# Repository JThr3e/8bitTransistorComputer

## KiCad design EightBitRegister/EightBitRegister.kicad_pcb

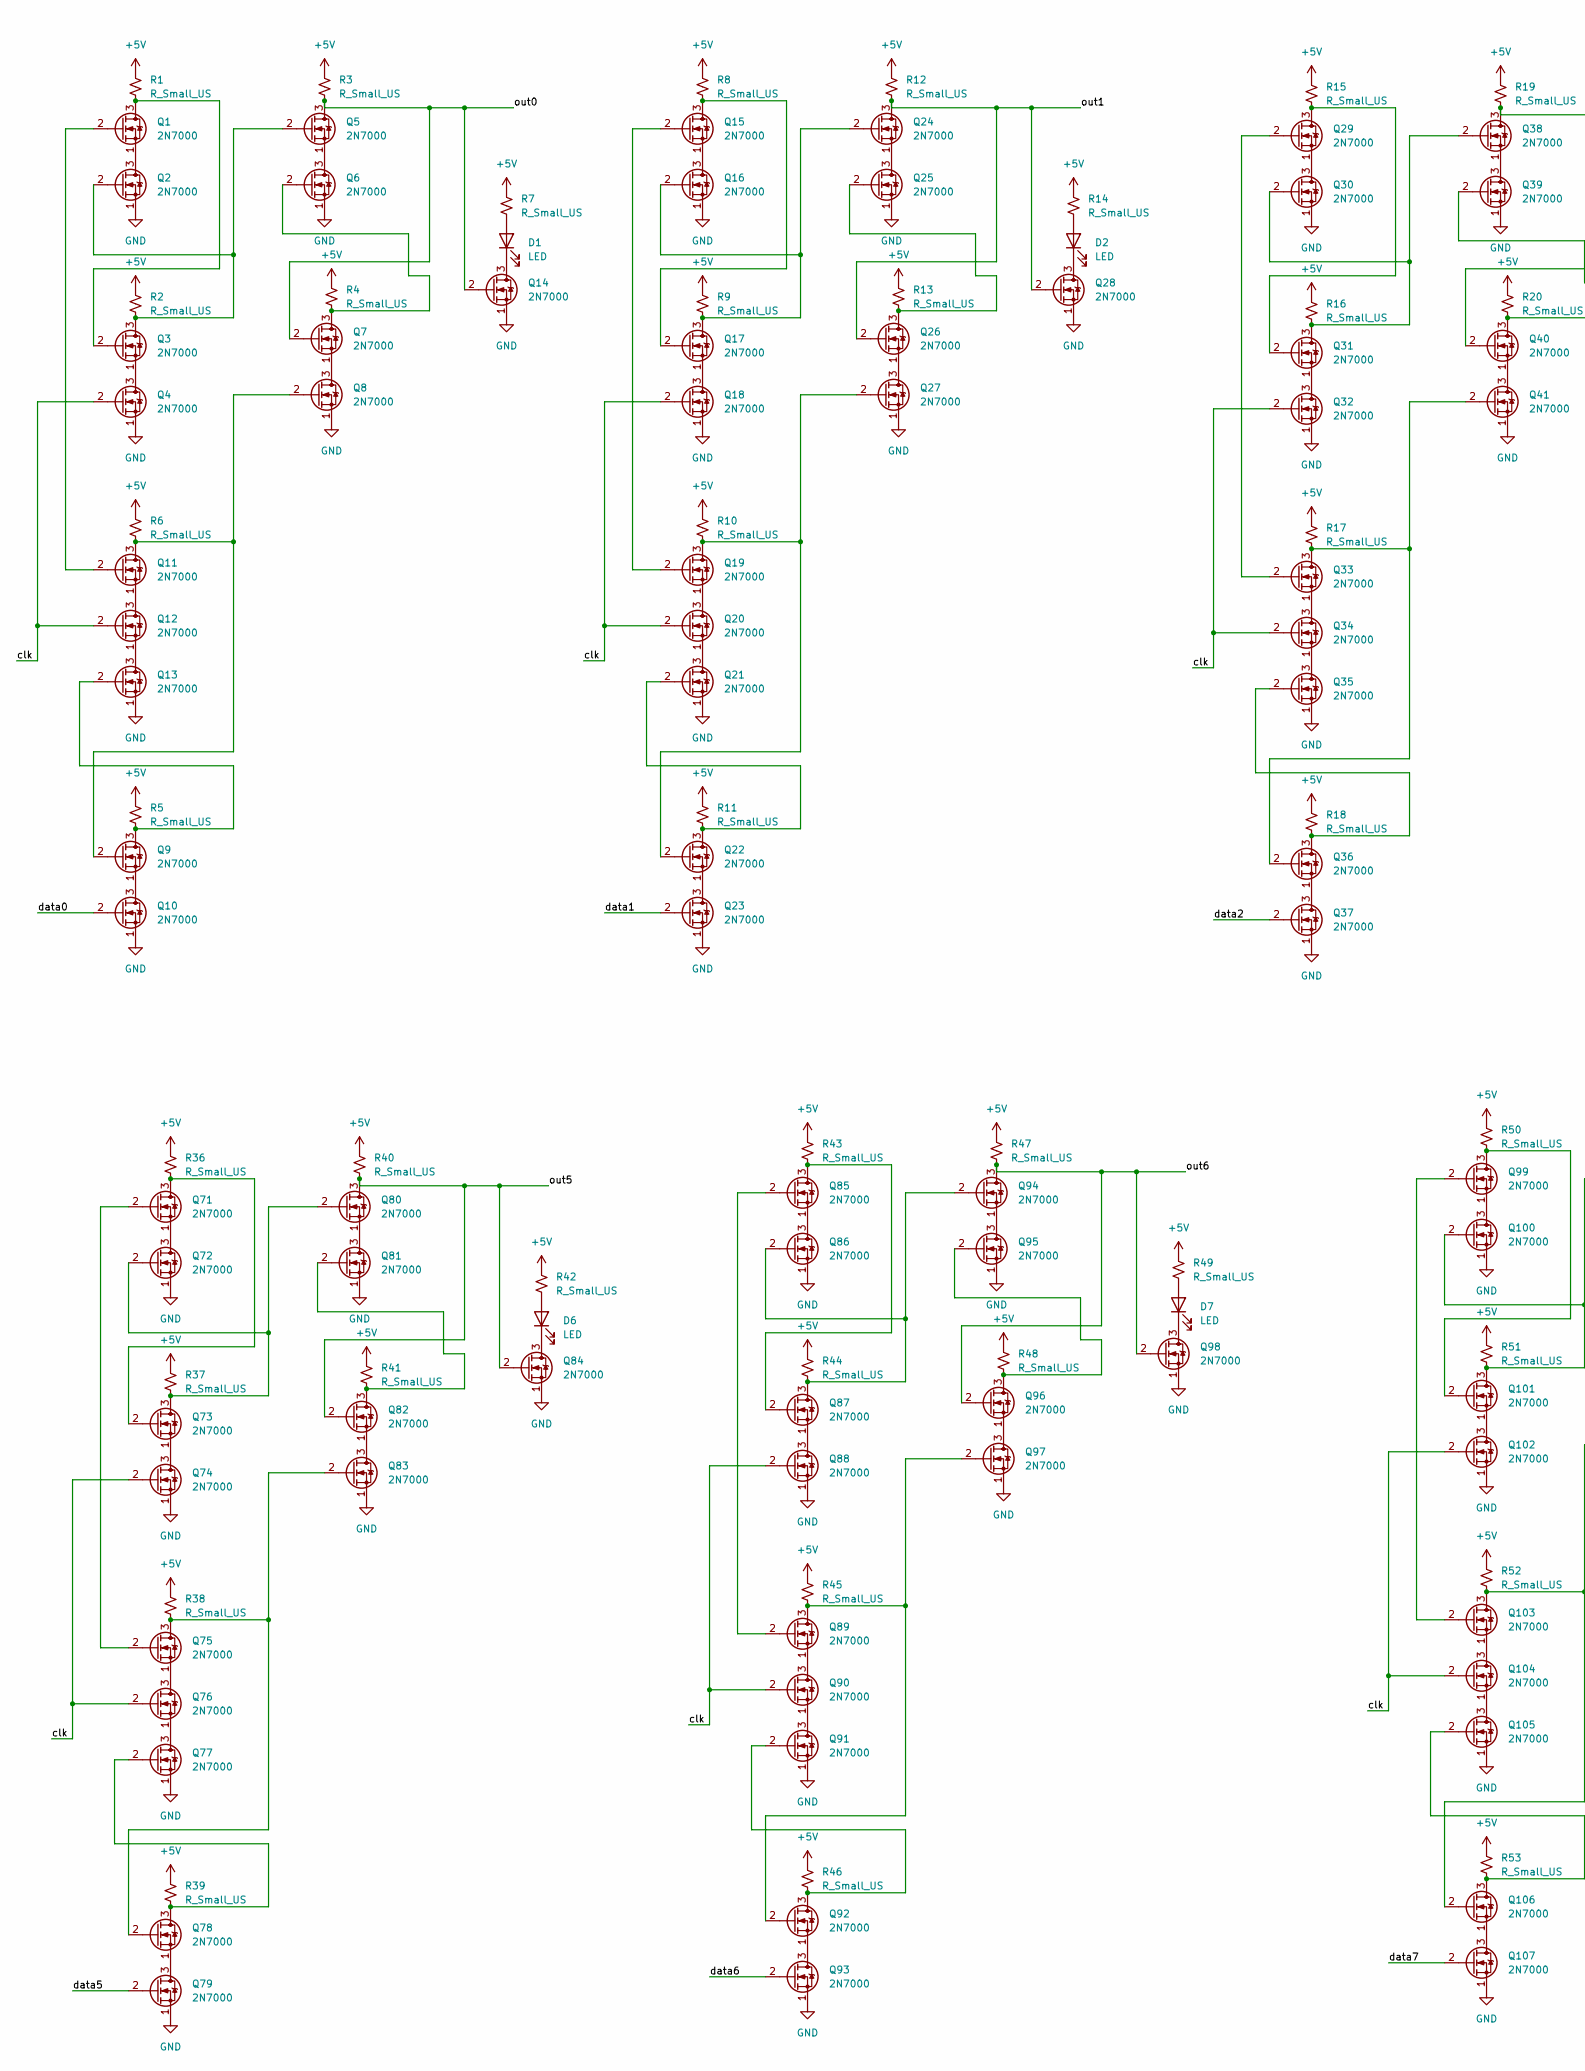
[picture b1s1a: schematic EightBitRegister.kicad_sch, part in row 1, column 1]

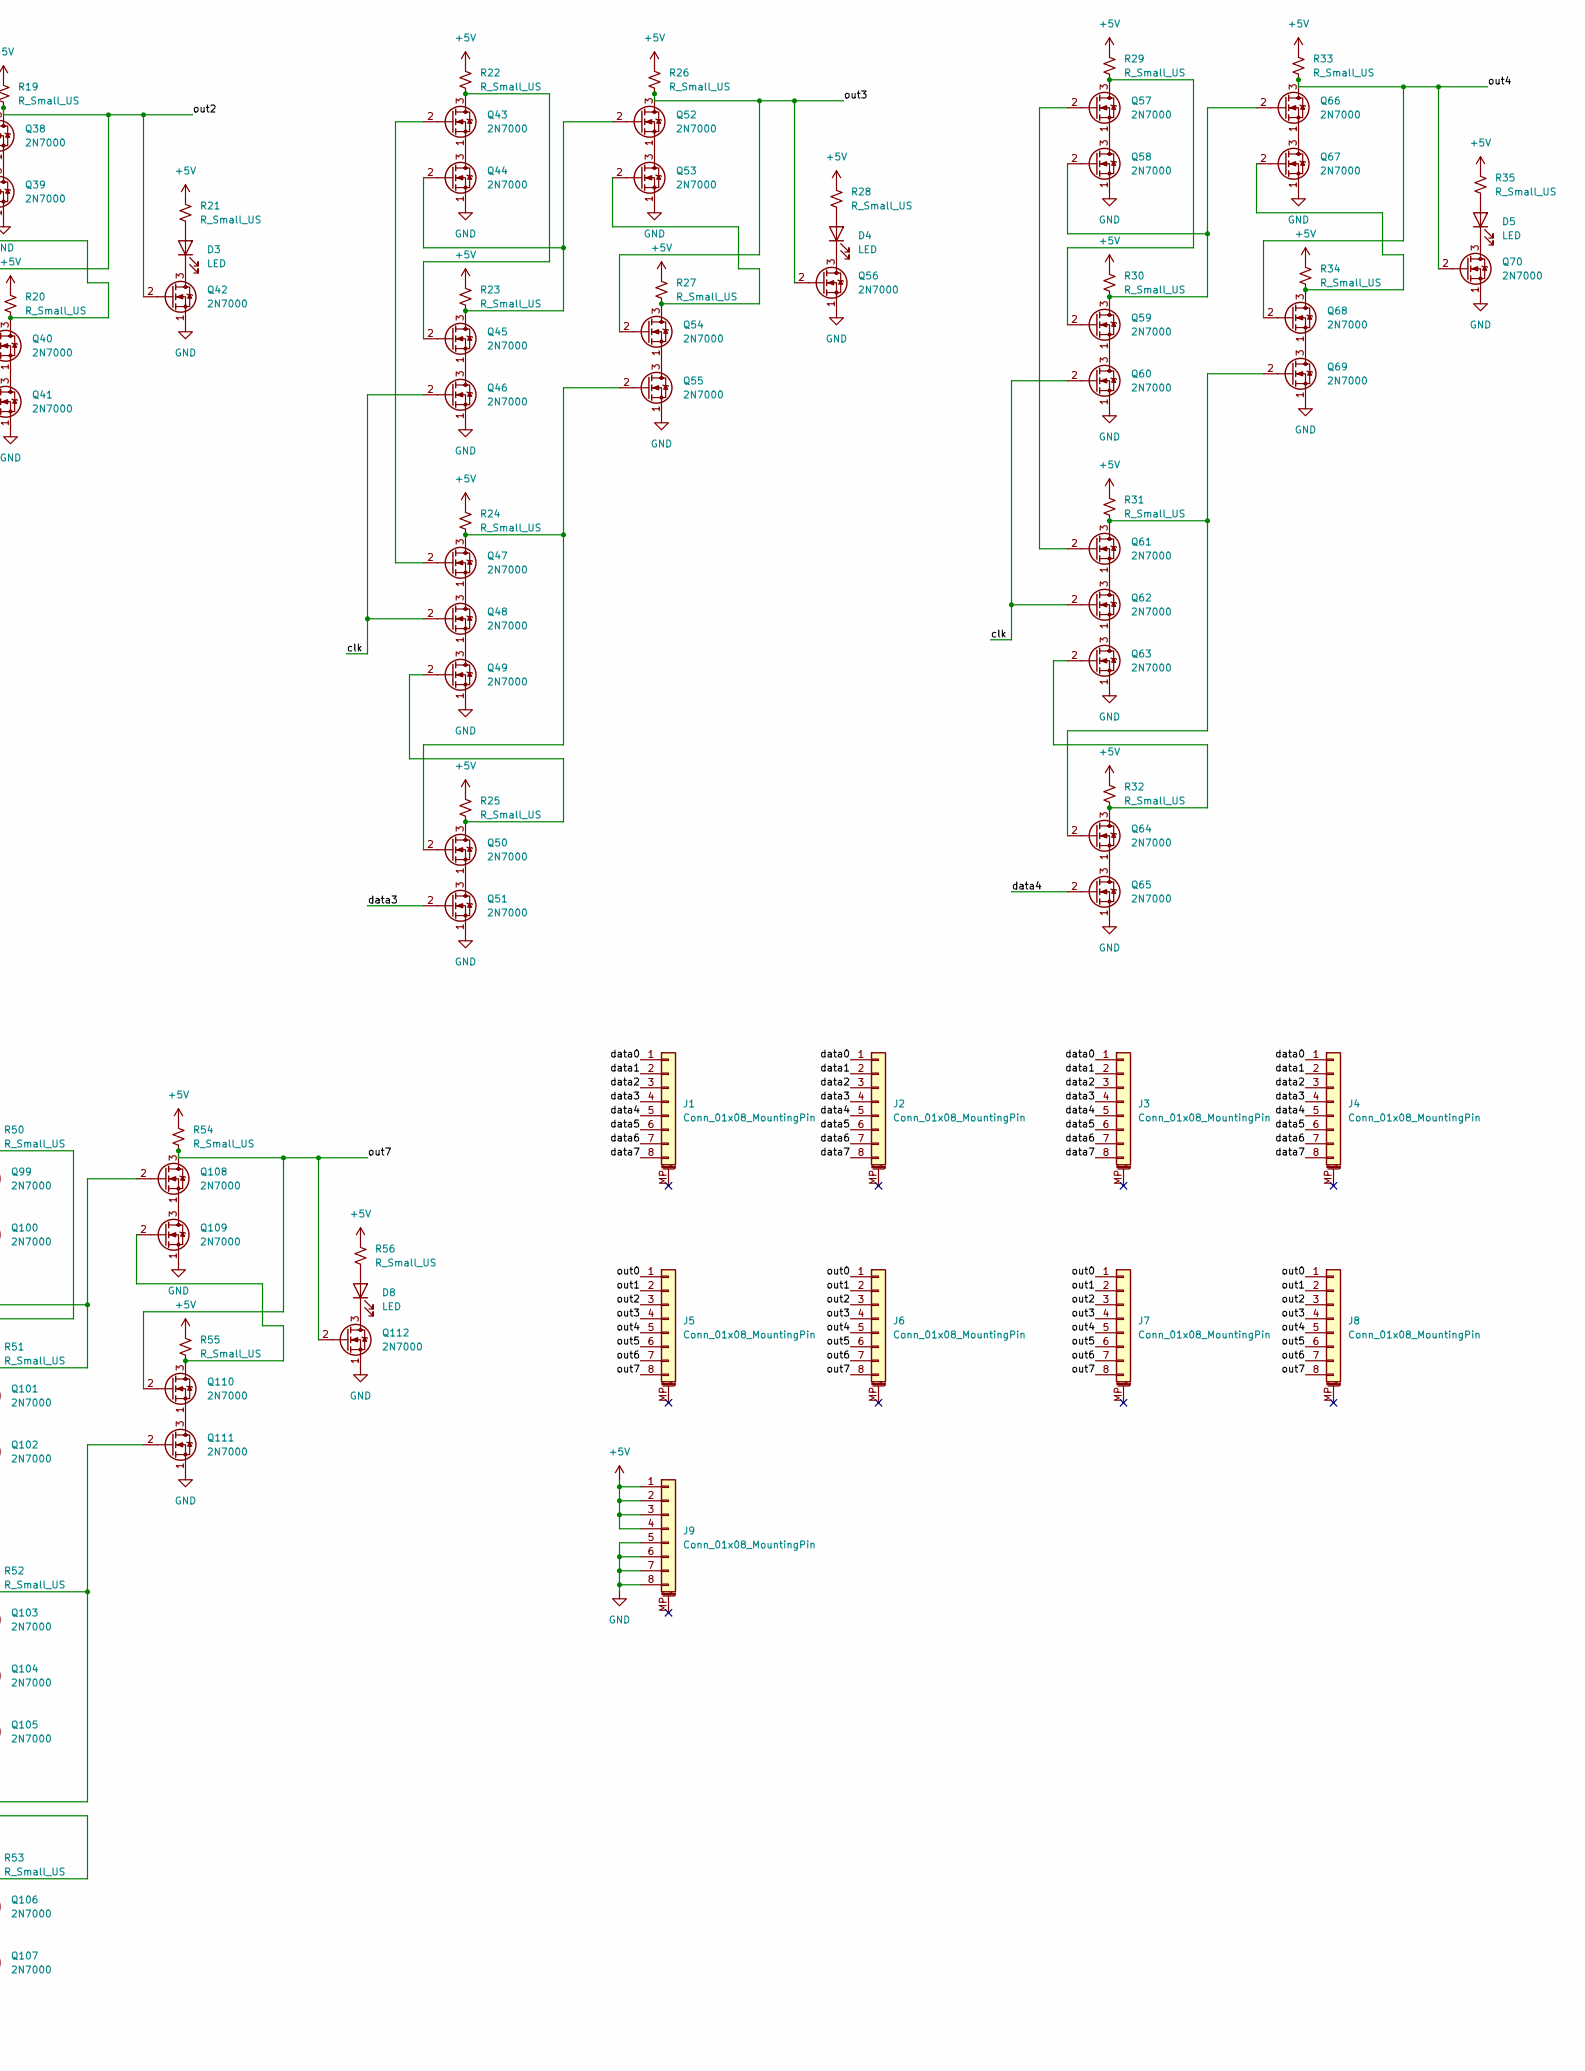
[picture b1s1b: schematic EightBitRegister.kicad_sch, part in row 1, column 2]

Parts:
D1, D2, D3, D4, D5, D6, D7, D8: LED; LED_D5.0mm
J1, J2, J3, J4, J5, J6, J7, J8, J9: Conn_01x08_MountingPin; PinSocket_1x08_P2.54mm_Vertical
Q1, Q2, Q3, Q4, Q5, Q6, Q7, Q8, Q9, Q10, Q11, Q12, Q13, Q14, Q15, Q16, Q17, Q18, Q19, Q20, Q21, Q22, Q23, Q24, Q25, Q26, Q27, Q28, Q29, Q30, Q31, Q32, Q33, Q34, Q35, Q36, Q37, Q38, Q39, Q40, Q41, Q42, Q43, Q44, Q45, Q46, Q47, Q48, Q49, Q50, Q51, Q52, Q53, Q54, Q55, Q56, Q57, Q58, Q59, Q60, Q61, Q62, Q63, Q64, Q65, Q66, Q67, Q68, Q69, Q70, Q71, Q72, Q73, Q74, Q75, Q76, Q77, Q78, Q79, Q80, Q81, Q82, Q83, Q84, Q85, Q86, Q87, Q88, Q89, Q90, Q91, Q92, Q93, Q94, Q95, Q96, Q97, Q98, Q99, Q100, Q101, Q102, Q103, Q104, Q105, Q106, Q107, Q108, Q109, Q110, Q111, Q112: 2N7000; TO-92_Inline
R1, R2, R3, R4, R5, R6, R7, R8, R9, R10, R11, R12, R13, R14, R15, R16, R17, R18, R19, R20, R21, R22, R23, R24, R25, R26, R27, R28, R29, R30, R31, R32, R33, R34, R35, R36, R37, R38, R39, R40, R41, R42, R43, R44, R45, R46, R47, R48, R49, R50, R51, R52, R53, R54, R55, R56: R_Small_US; R_0805_2012Metric_Pad1.20x1.40mm_HandSolder

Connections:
+5V: J9.1, J9.2, J9.3, J9.4, R1.1, R2.1, R3.1, R4.1, R5.1, R6.1, R7.1, R8.1, R9.1, R10.1, R11.1, R12.1, R13.1, R14.1, R15.1, R16.1, R17.1, R18.1, R19.1, R20.1, R21.1, R22.1, R23.1, R24.1, R25.1, R26.1, R27.1, R28.1, R29.1, R30.1, R31.1, R32.1, R33.1, R34.1, R35.1, R36.1, R37.1, R38.1, R39.1, R40.1, R41.1, R42.1, R43.1, R44.1, R45.1, R46.1, R47.1, R48.1, R49.1, R50.1, R51.1, R52.1, R53.1, R54.1, R55.1, R56.1
/clk: Q4.2 (G), Q12.2 (G), Q18.2 (G), Q20.2 (G), Q32.2 (G), Q34.2 (G), Q46.2 (G), Q48.2 (G), Q60.2 (G), Q62.2 (G), Q74.2 (G), Q76.2 (G), Q88.2 (G), Q90.2 (G), Q102.2 (G), Q104.2 (G)
/data0: J1.1, J2.1, J3.1, J4.1, Q10.2 (G)
/data1: J1.2, J2.2, J3.2, J4.2, Q23.2 (G)
/data2: J1.3, J2.3, J3.3, J4.3, Q37.2 (G)
/data3: J1.4, J2.4, J3.4, J4.4, Q51.2 (G)
/data4: J1.5, J2.5, J3.5, J4.5, Q65.2 (G)
/data5: J1.6, J2.6, J3.6, J4.6, Q79.2 (G)
/data6: J1.7, J2.7, J3.7, J4.7, Q93.2 (G)
/data7: J1.8, J2.8, J3.8, J4.8, Q107.2 (G)
/out0: J5.1, J6.1, J7.1, J8.1, Q5.3 (D), Q7.2 (G), Q14.2 (G), R3.2
/out1: J5.2, J6.2, J7.2, J8.2, Q24.3 (D), Q26.2 (G), Q28.2 (G), R12.2
/out2: J5.3, J6.3, J7.3, J8.3, Q38.3 (D), Q40.2 (G), Q42.2 (G), R19.2
/out3: J5.4, J6.4, J7.4, J8.4, Q52.3 (D), Q54.2 (G), Q56.2 (G), R26.2
/out4: J5.5, J6.5, J7.5, J8.5, Q66.3 (D), Q68.2 (G), Q70.2 (G), R33.2
/out5: J5.6, J6.6, J7.6, J8.6, Q80.3 (D), Q82.2 (G), Q84.2 (G), R40.2
/out6: J5.7, J6.7, J7.7, J8.7, Q94.3 (D), Q96.2 (G), Q98.2 (G), R47.2
/out7: J5.8, J6.8, J7.8, J8.8, Q108.3 (D), Q110.2 (G), Q112.2 (G), R54.2
GND: J9.5, J9.6, J9.7, J9.8, Q2.1 (S), Q4.1 (S), Q6.1 (S), Q8.1 (S), Q10.1 (S), Q13.1 (S), Q14.1 (S), Q16.1 (S), Q18.1 (S), Q21.1 (S), Q23.1 (S), Q25.1 (S), Q27.1 (S), Q28.1 (S), Q30.1 (S), Q32.1 (S), Q35.1 (S), Q37.1 (S), Q39.1 (S), Q41.1 (S), Q42.1 (S), Q44.1 (S), Q46.1 (S), Q49.1 (S), Q51.1 (S), Q53.1 (S), Q55.1 (S), Q56.1 (S), Q58.1 (S), Q60.1 (S), Q63.1 (S), Q65.1 (S), Q67.1 (S), Q69.1 (S), Q70.1 (S), Q72.1 (S), Q74.1 (S), Q77.1 (S), Q79.1 (S), Q81.1 (S), Q83.1 (S), Q84.1 (S), Q86.1 (S), Q88.1 (S), Q91.1 (S), Q93.1 (S), Q95.1 (S), Q97.1 (S), Q98.1 (S), Q100.1 (S), Q102.1 (S), Q105.1 (S), Q107.1 (S), Q109.1 (S), Q111.1 (S), Q112.1 (S)
unnamed: D1.2 (A), R7.2
unnamed: D1.1 (K), Q14.3 (D)
unnamed: D2.2 (A), R14.2
unnamed: D2.1 (K), Q28.3 (D)
unnamed: D3.2 (A), R21.2
unnamed: D3.1 (K), Q42.3 (D)
unnamed: D4.2 (A), R28.2
unnamed: D4.1 (K), Q56.3 (D)
unnamed: D5.2 (A), R35.2
unnamed: D5.1 (K), Q70.3 (D)
unnamed: D6.2 (A), R42.2
unnamed: D6.1 (K), Q84.3 (D)
unnamed: D7.2 (A), R49.2
unnamed: D7.1 (K), Q98.3 (D)
unnamed: D8.2 (A), R56.2
unnamed: D8.1 (K), Q112.3 (D)
unnamed: Q1.3 (D), Q3.2 (G), R1.2
unnamed: Q1.2 (G), Q11.2 (G)
unnamed: Q1.1 (S), Q2.3 (D)
unnamed: Q2.2 (G), Q3.3 (D), Q5.2 (G), R2.2
unnamed: Q3.1 (S), Q4.3 (D)
unnamed: Q5.1 (S), Q6.3 (D)
unnamed: Q6.2 (G), Q7.3 (D), R4.2
unnamed: Q7.1 (S), Q8.3 (D)
unnamed: Q9.1 (S), Q10.3 (D)
unnamed: Q8.2 (G), Q9.2 (G), Q11.3 (D), R6.2
unnamed: Q11.1 (S), Q12.3 (D)
unnamed: Q12.1 (S), Q13.3 (D)
unnamed: Q9.3 (D), Q13.2 (G), R5.2
unnamed: Q15.3 (D), Q17.2 (G), R8.2
unnamed: Q15.2 (G), Q19.2 (G)
unnamed: Q15.1 (S), Q16.3 (D)
unnamed: Q16.2 (G), Q17.3 (D), Q24.2 (G), R9.2
unnamed: Q17.1 (S), Q18.3 (D)
unnamed: Q19.3 (D), Q22.2 (G), Q27.2 (G), R10.2
unnamed: Q19.1 (S), Q20.3 (D)
unnamed: Q20.1 (S), Q21.3 (D)
unnamed: Q21.2 (G), Q22.3 (D), R11.2
unnamed: Q22.1 (S), Q23.3 (D)
unnamed: Q24.1 (S), Q25.3 (D)
unnamed: Q25.2 (G), Q26.3 (D), R13.2
unnamed: Q26.1 (S), Q27.3 (D)
unnamed: Q29.3 (D), Q31.2 (G), R15.2
unnamed: Q29.2 (G), Q33.2 (G)
unnamed: Q29.1 (S), Q30.3 (D)
unnamed: Q30.2 (G), Q31.3 (D), Q38.2 (G), R16.2
unnamed: Q31.1 (S), Q32.3 (D)
unnamed: Q33.3 (D), Q36.2 (G), Q41.2 (G), R17.2
unnamed: Q33.1 (S), Q34.3 (D)
unnamed: Q34.1 (S), Q35.3 (D)
unnamed: Q35.2 (G), Q36.3 (D), R18.2
unnamed: Q36.1 (S), Q37.3 (D)
unnamed: Q38.1 (S), Q39.3 (D)
unnamed: Q39.2 (G), Q40.3 (D), R20.2
unnamed: Q40.1 (S), Q41.3 (D)
unnamed: Q43.3 (D), Q45.2 (G), R22.2
unnamed: Q43.2 (G), Q47.2 (G)
unnamed: Q43.1 (S), Q44.3 (D)
unnamed: Q44.2 (G), Q45.3 (D), Q52.2 (G), R23.2
unnamed: Q45.1 (S), Q46.3 (D)
unnamed: Q47.3 (D), Q50.2 (G), Q55.2 (G), R24.2
unnamed: Q47.1 (S), Q48.3 (D)
unnamed: Q48.1 (S), Q49.3 (D)
unnamed: Q49.2 (G), Q50.3 (D), R25.2
unnamed: Q50.1 (S), Q51.3 (D)
unnamed: Q52.1 (S), Q53.3 (D)
unnamed: Q53.2 (G), Q54.3 (D), R27.2
unnamed: Q54.1 (S), Q55.3 (D)
unnamed: Q57.3 (D), Q59.2 (G), R29.2
unnamed: Q57.2 (G), Q61.2 (G)
unnamed: Q57.1 (S), Q58.3 (D)
unnamed: Q58.2 (G), Q59.3 (D), Q66.2 (G), R30.2
unnamed: Q59.1 (S), Q60.3 (D)
unnamed: Q61.3 (D), Q64.2 (G), Q69.2 (G), R31.2
unnamed: Q61.1 (S), Q62.3 (D)
unnamed: Q62.1 (S), Q63.3 (D)
unnamed: Q63.2 (G), Q64.3 (D), R32.2
unnamed: Q64.1 (S), Q65.3 (D)
unnamed: Q66.1 (S), Q67.3 (D)
unnamed: Q67.2 (G), Q68.3 (D), R34.2
unnamed: Q68.1 (S), Q69.3 (D)
unnamed: Q71.3 (D), Q73.2 (G), R36.2
unnamed: Q71.2 (G), Q75.2 (G)
unnamed: Q71.1 (S), Q72.3 (D)
unnamed: Q72.2 (G), Q73.3 (D), Q80.2 (G), R37.2
unnamed: Q73.1 (S), Q74.3 (D)
unnamed: Q75.3 (D), Q78.2 (G), Q83.2 (G), R38.2
unnamed: Q75.1 (S), Q76.3 (D)
unnamed: Q76.1 (S), Q77.3 (D)
unnamed: Q77.2 (G), Q78.3 (D), R39.2
unnamed: Q78.1 (S), Q79.3 (D)
unnamed: Q80.1 (S), Q81.3 (D)
unnamed: Q81.2 (G), Q82.3 (D), R41.2
unnamed: Q82.1 (S), Q83.3 (D)
unnamed: Q85.3 (D), Q87.2 (G), R43.2
unnamed: Q85.2 (G), Q89.2 (G)
unnamed: Q85.1 (S), Q86.3 (D)
unnamed: Q86.2 (G), Q87.3 (D), Q94.2 (G), R44.2
unnamed: Q87.1 (S), Q88.3 (D)
unnamed: Q89.3 (D), Q92.2 (G), Q97.2 (G), R45.2
unnamed: Q89.1 (S), Q90.3 (D)
unnamed: Q90.1 (S), Q91.3 (D)
unnamed: Q91.2 (G), Q92.3 (D), R46.2
unnamed: Q92.1 (S), Q93.3 (D)
unnamed: Q94.1 (S), Q95.3 (D)
unnamed: Q95.2 (G), Q96.3 (D), R48.2
unnamed: Q96.1 (S), Q97.3 (D)
unnamed: Q99.1 (S), Q100.3 (D)
unnamed: Q100.2 (G), Q101.3 (D), Q108.2 (G), R51.2
unnamed: Q99.3 (D), Q101.2 (G), R50.2
unnamed: Q101.1 (S), Q102.3 (D)
unnamed: Q103.3 (D), Q106.2 (G), Q111.2 (G), R52.2
unnamed: Q99.2 (G), Q103.2 (G)
unnamed: Q103.1 (S), Q104.3 (D)
unnamed: Q104.1 (S), Q105.3 (D)
unnamed: Q105.2 (G), Q106.3 (D), R53.2
unnamed: Q106.1 (S), Q107.3 (D)
unnamed: Q108.1 (S), Q109.3 (D)
unnamed: Q109.2 (G), Q110.3 (D), R55.2
unnamed: Q110.1 (S), Q111.3 (D)

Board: 2 copper layers, 185 parts (0 on the bottom side), 139 nets, no tracks yet.
